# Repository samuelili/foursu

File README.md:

# foursu
 pcb for the foursu mocupad

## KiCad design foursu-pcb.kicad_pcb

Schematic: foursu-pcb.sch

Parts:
C1, C2, C5: 0.1uF; C_0805_2012Metric
C3, C4: 22pF; C_0805_2012Metric
C6: 10uF; C_0805_2012Metric
C7: 1uF; C_0805_2012Metric
D1, D2, D3, D4, D5: SOD-123; D_SOD-123
F1: Polyfuse; Fuse_1206_3216Metric
J1: USB_C_Receptacle_USB2.0; USB_C_Receptacle_Amphenol_12401548E4-2A
MX1, MX2, MX3, MX4: MX-NoLED; MX-1U-NoLED
R1, R2: 22; R_0805_2012Metric
R3, R4: 10k; R_0805_2012Metric
R5, R6: 5.1K; R_0805_2012Metric
SW1: Rotary_Encoder_Switch; RotaryEncoder_Alps_EC11E-Switch_Vertical_H20mm
SW2: SW_Push; SKQG-1155865
U1: ATmega32U4-AU; TQFP-44_10x10mm_P0.8mm
Y1: 16MHz; Crystal_SMD_3225-4Pin_3.2x2.5mm

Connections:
+5V: C1.1, C2.1, C5.1, C6.1, F1.1, R3.1, U1.2, U1.7, U1.14, U1.24, U1.34, U1.44
COL0: MX1.1 (COL), U1.36
COL1: MX2.1 (COL), U1.37
COL2: MX3.1 (COL), U1.38
COL3: MX4.1 (COL), U1.39
COL4: SW1.S2, U1.40
D+: J1.B6, R2.2
D-: J1.B7, R1.2
ENC0: SW1.B, U1.21
ENC1: SW1.A, U1.22
GND: C1.2, C2.2, C3.2, C4.2, C5.2, C6.2, C7.2, J1.A1, J1.A12, J1.B1, J1.B12, R4.1, R5.1, R6.1, SW1.C, SW2.1, U1.5, U1.15, U1.23, U1.35, U1.43, Y1.2, Y1.4
unnamed: C3.1, U1.17, Y1.1
unnamed: C4.1, U1.16, Y1.3
unnamed: C7.1, U1.6
unnamed: D1.2, MX1.2 (ROW)
unnamed: D2.2, MX2.2 (ROW)
unnamed: D3.2, MX3.2 (ROW)
unnamed: D4.2, MX4.2 (ROW)
unnamed: D5.2, SW1.S1
unnamed: J1.A5, R5.2
unnamed: J1.B5, R6.2
unnamed: R1.1, U1.3
unnamed: R2.1, U1.4
unnamed: R3.2, SW2.2, U1.13
unnamed: R4.2, U1.33
ROW0: D1.1, D2.1, D3.1, D4.1, D5.1, U1.41
VCC: F1.2, J1.A4, J1.A9, J1.B4, J1.B9

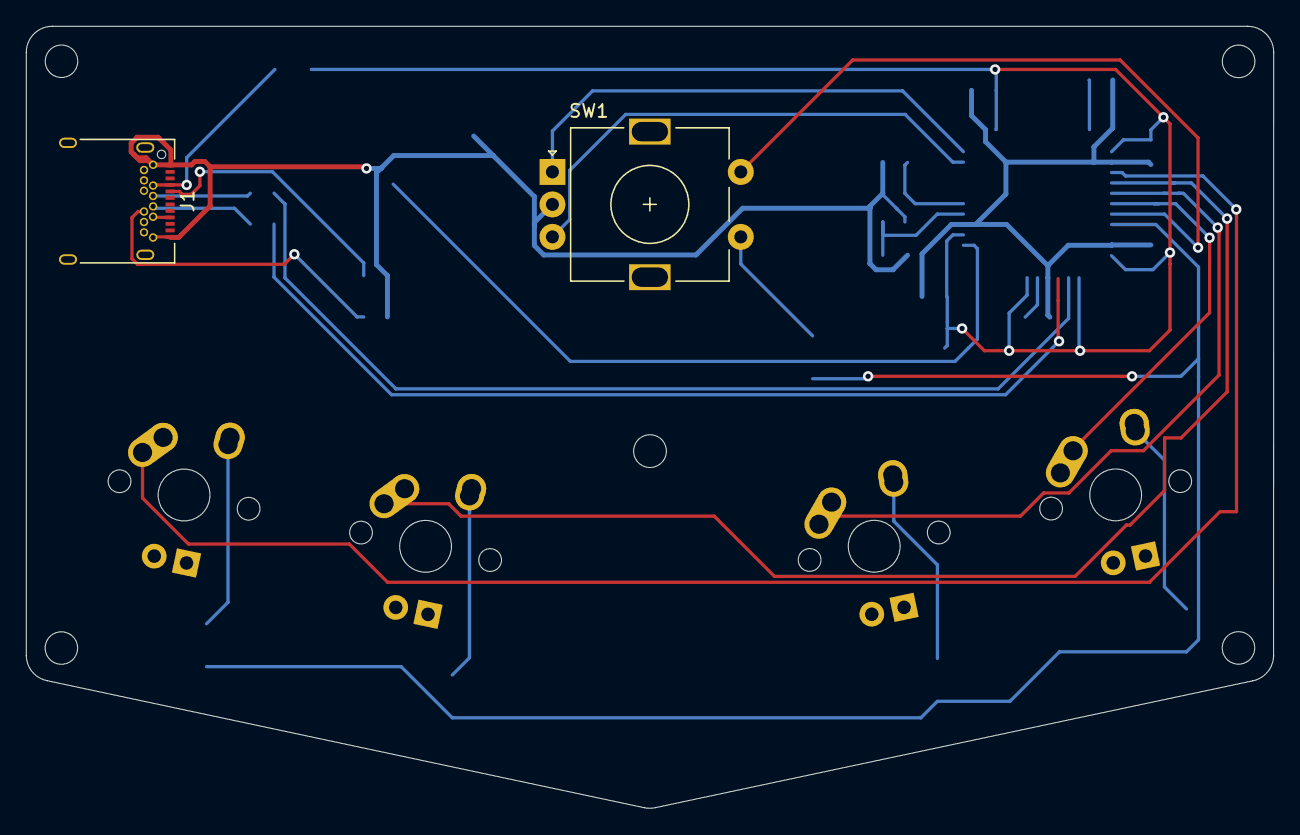
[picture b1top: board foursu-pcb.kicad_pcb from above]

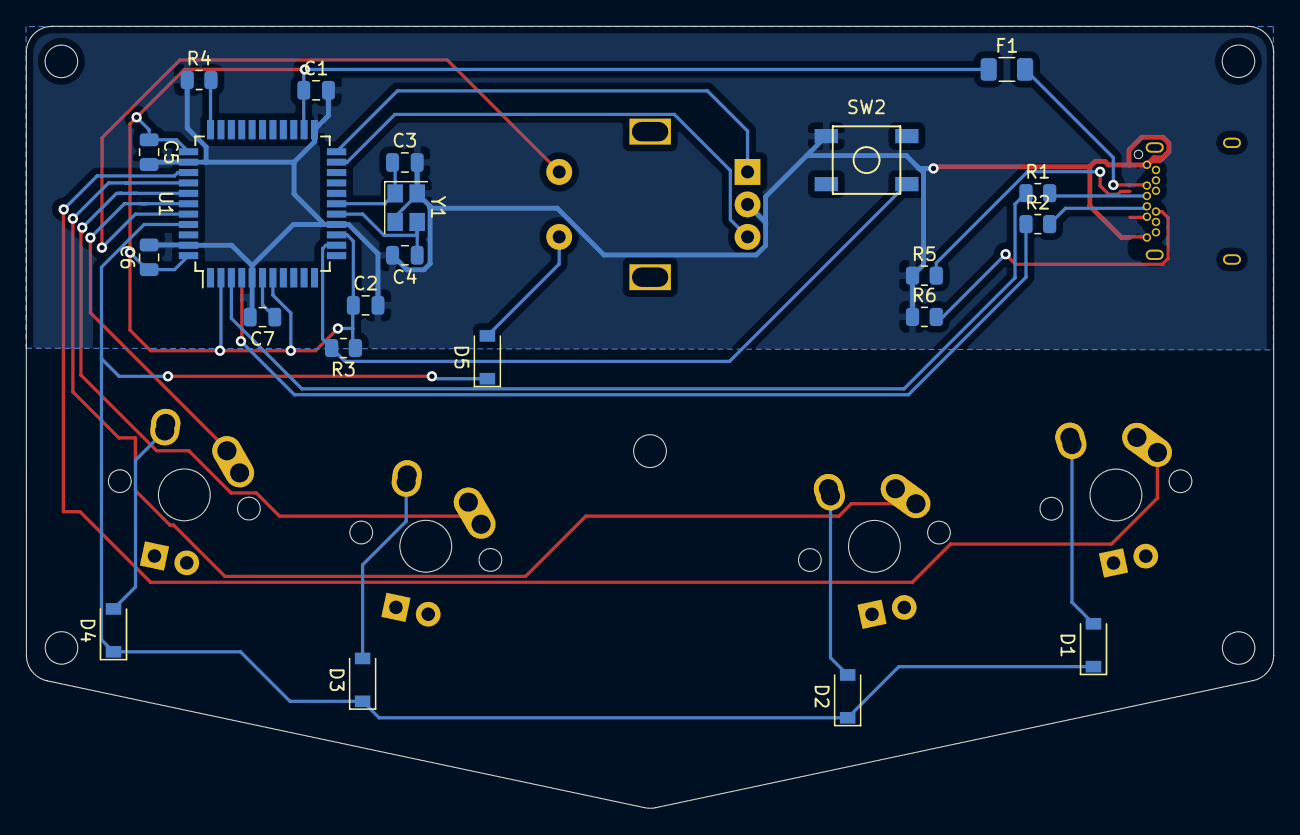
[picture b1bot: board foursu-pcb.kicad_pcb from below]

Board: 2 copper layers, 96.0 x 60.2 mm, 28 parts (22 on the bottom side), 27 nets.

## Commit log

2021-01-21 add submodules
2021-01-21 add footprint libraries
2021-01-27 ah yes a commit
2021-01-28 uh yes microcontroller stuff
2021-01-29 finished first prototype?
2021-02-05 files for initial prototype
2021-02-05 cleaned up files
2021-03-06 finished pcb routing
2021-06-11 some commit idk
